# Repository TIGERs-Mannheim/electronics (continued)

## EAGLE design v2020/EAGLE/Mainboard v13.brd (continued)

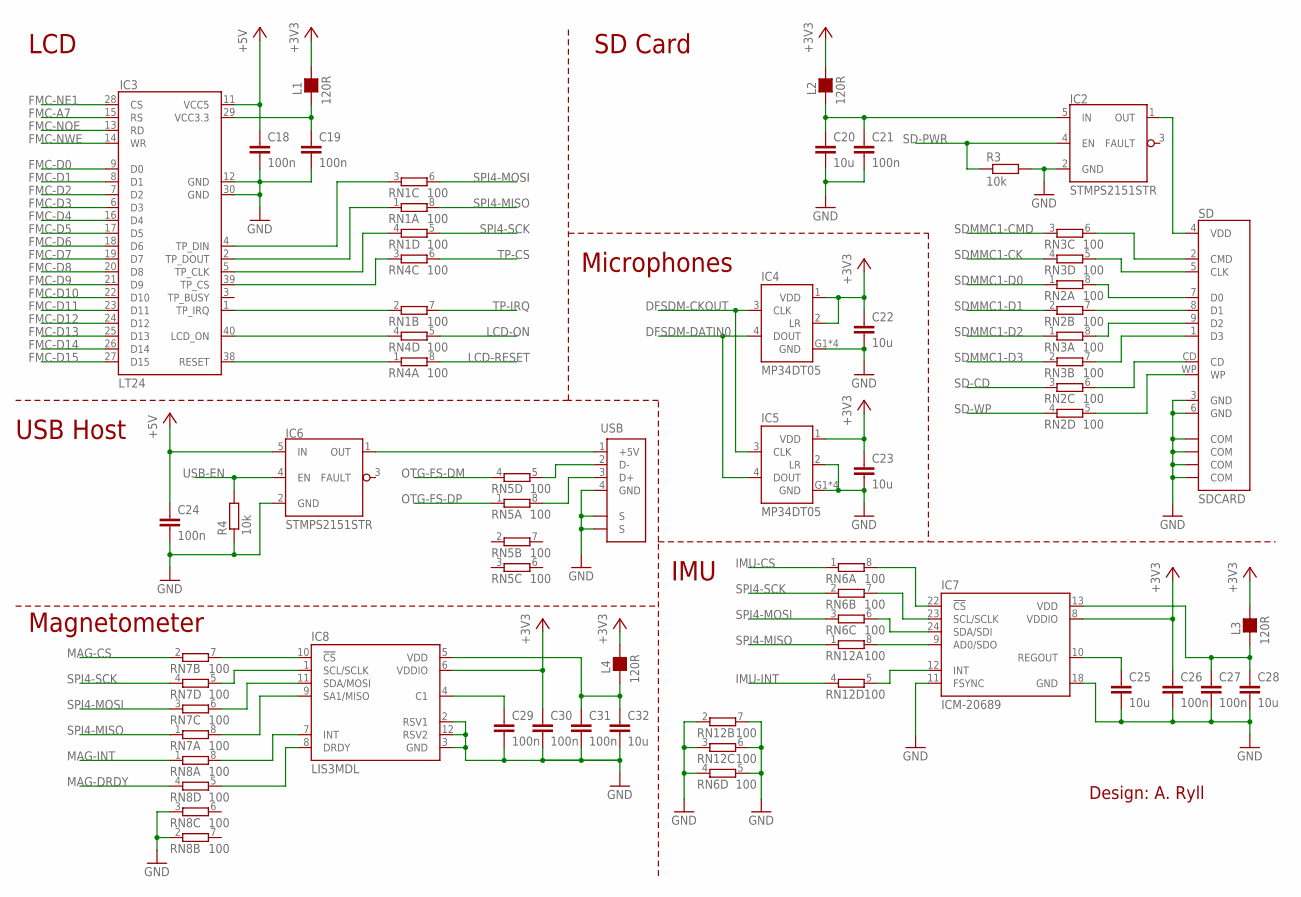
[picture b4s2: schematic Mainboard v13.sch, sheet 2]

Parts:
C18, C19, C21, C24, C26, C27, C29, C30, C31: 100n; C0603
C20, C22, C23, C25, C28, C32: 10u; C0603
IC2, IC6: STMPS2151STR; SOT23-5
IC3: LT24
IC4, IC5: MP34DT05; HCLGA4
IC7: ICM-20689; QFN24-4X4-P
IC8: LIS3MDL; VFLGA-12
L1, L2, L3, L4: 120R; L0603
R3, R4: 10k; R0603
RN1, RN2, RN3, RN4, RN5, RN6, RN7, RN8, RN12: 100; EXB28V
SD: SDCARD
USB: USBATE; USBA-TE

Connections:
+3V3: C22.1, C23.1, C26.1, C30.1, IC4.1 (VDD), IC4.2 (LR), IC5.1 (VDD), IC7.8 (VDDIO), IC8.6 (VDDIO), L1.2, L2.2, L3.2, L4.2; also elsewhere on the board
+5V: C18.1, C24.1, IC3.11 (VCC5), IC6.5 (IN); also elsewhere on the board
DFSDM-CKOUT: IC4.3 (CLK), IC5.3 (CLK); also elsewhere on the board
DFSDM-DATIN0: IC4.4 (DOUT), IC5.4 (DOUT); also elsewhere on the board
FMC-A7: IC3.15 (RS); also elsewhere on the board
FMC-D0: IC3.9 (D0); also elsewhere on the board
FMC-D1: IC3.8 (D1); also elsewhere on the board
FMC-D2: IC3.7 (D2); also elsewhere on the board
FMC-D3: IC3.6 (D3); also elsewhere on the board
FMC-D4: IC3.16 (D4); also elsewhere on the board
FMC-D5: IC3.17 (D5); also elsewhere on the board
FMC-D6: IC3.18 (D6); also elsewhere on the board
FMC-D7: IC3.19 (D7); also elsewhere on the board
FMC-D8: IC3.20 (D8); also elsewhere on the board
FMC-D9: IC3.21 (D9); also elsewhere on the board
FMC-D10: IC3.22 (D10); also elsewhere on the board
FMC-D11: IC3.23 (D11); also elsewhere on the board
FMC-D12: IC3.24 (D12); also elsewhere on the board
FMC-D13: IC3.25 (D13); also elsewhere on the board
FMC-D14: IC3.26 (D14); also elsewhere on the board
FMC-D15: IC3.27 (D15); also elsewhere on the board
FMC-NE1: IC3.28 (CS); also elsewhere on the board
FMC-NOE: IC3.13 (RD); also elsewhere on the board
FMC-NWE: IC3.14 (WR); also elsewhere on the board
GND: C18.2, C19.2, C20.2, C21.2, C22.2, C23.2, C24.2, C25.2, C26.2, C27.2, C28.2, C29.2, C30.2, C31.2, C32.2, IC2.2 (GND), IC3.12 (GND), IC3.30 (GND), IC4.G1 (GND), IC4.G2 (GND), IC4.G3 (GND), IC4.G4 (GND), IC5.2 (LR), IC5.G1 (GND), IC5.G2 (GND), IC5.G3 (GND), IC5.G4 (GND), IC6.2 (GND), IC7.11 (FSYNC), IC7.18 (GND), IC8.2 (RSV1), IC8.3 (GND), IC8.12 (RSV2), R3.2, R4.1, RN6.4 (1), RN6.5 (2), RN8.2 (1), RN8.3 (1), RN12.2 (1), RN12.3 (1), RN12.6 (2), RN12.7 (2), SD.3 (GND), SD.6 (GND), SD.COM1 (COM), SD.COM2 (COM), SD.COM3 (COM), SD.COM4 (COM), USB.4 (GND), USB.MNT1 (S), USB.MNT2 (S); also elsewhere on the board
IMU-CS: RN6.1; also elsewhere on the board
IMU-INT: RN12.4 (1); also elsewhere on the board
LCD-ON: RN4.5 (2); also elsewhere on the board
LCD-RESET: RN4.8 (2); also elsewhere on the board
MAG-CS: RN7.2 (1); also elsewhere on the board
MAG-DRDY: RN8.4 (1); also elsewhere on the board
MAG-INT: RN8.1; also elsewhere on the board
unnamed: IC8.10 (!CS), RN7.7 (2)
unnamed: IC8.1 (SCL/SCLK), RN7.5 (2)
unnamed: IC8.11 (SDA/MOSI), RN7.6 (2)
unnamed: IC8.9 (SA1/MISO), RN7.8 (2)
unnamed: IC8.7 (INT), RN8.8 (2)
unnamed: IC8.8 (DRDY), RN8.5 (2)
unnamed: C29.1, IC8.4 (C1)
unnamed: C31.1, C32.1, IC8.5 (VDD), L4.1
unnamed: IC7.12 (INT), RN12.5 (2)
unnamed: C19.1, IC3.29 (VCC3.3), L1.1
unnamed: IC3.38 (RESET), RN4.1
unnamed: IC3.40 (LCD_ON), RN4.4 (1)
unnamed: IC3.1 (TP_IRQ), RN1.2 (1)
unnamed: IC3.39 (TP_CS), RN4.3 (1)
unnamed: IC3.5 (TP_CLK), RN1.4 (1)
unnamed: IC3.2 (TP_DOUT), RN1.1
unnamed: IC3.4 (TP_DIN), RN1.3 (1)
unnamed: RN2.7 (2), SD.8 (D1)
unnamed: RN2.8 (2), SD.7 (D0)
unnamed: RN3.5 (2), SD.5 (CLK)
unnamed: RN3.6 (2), SD.2 (CMD)
unnamed: RN3.8 (2), SD.9 (D2)
unnamed: RN3.7 (2), SD.1 (D3)
unnamed: RN2.6 (2), SD.CD
unnamed: RN2.5 (2), SD.WP
unnamed: C20.1, C21.1, IC2.5 (IN), L2.1
unnamed: IC6.1 (OUT), USB.1 (+5V)
unnamed: RN5.5 (2), USB.2 (D-)
unnamed: RN5.8 (2), USB.3 (D+)
unnamed: IC7.9 (AD0/SDO), RN12.8 (2)
unnamed: C25.1, IC7.10 (REGOUT)
unnamed: C27.1, C28.1, IC7.13 (VDD), L3.1
unnamed: IC7.24 (SDA/SDI), RN6.6 (2)
unnamed: IC7.23 (SCL/SCLK), RN6.7 (2)
unnamed: IC7.22 (!CS), RN6.8 (2)
OTG-FS-DM: RN5.4 (1); also elsewhere on the board
OTG-FS-DP: RN5.1; also elsewhere on the board
SD-CD: RN2.3 (1); also elsewhere on the board
SD-PWR: IC2.4 (EN), R3.1; also elsewhere on the board
SD-WP: RN2.4 (1); also elsewhere on the board
SDMMC1-CK: RN3.4 (1); also elsewhere on the board
SDMMC1-CMD: RN3.3 (1); also elsewhere on the board
SDMMC1-D0: RN2.1; also elsewhere on the board
SDMMC1-D1: RN2.2 (1); also elsewhere on the board
SDMMC1-D2: RN3.1; also elsewhere on the board
SDMMC1-D3: RN3.2 (1); also elsewhere on the board
SD_PWR: IC2.1 (OUT), SD.4 (VDD)
SPI4-MISO: RN1.8 (2), RN7.1, RN12.1; also elsewhere on the board
SPI4-MOSI: RN1.6 (2), RN6.3 (1), RN7.3 (1); also elsewhere on the board
SPI4-SCK: RN1.5 (2), RN6.2 (1), RN7.4 (1); also elsewhere on the board
TP-CS: RN4.6 (2); also elsewhere on the board
TP-IRQ: RN1.7 (2); also elsewhere on the board
USB-EN: IC6.4 (EN), R4.2; also elsewhere on the board

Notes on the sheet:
Design: A. Ryll
LCD
Microphones
SD Card
USB Host
Magnetometer
IMU

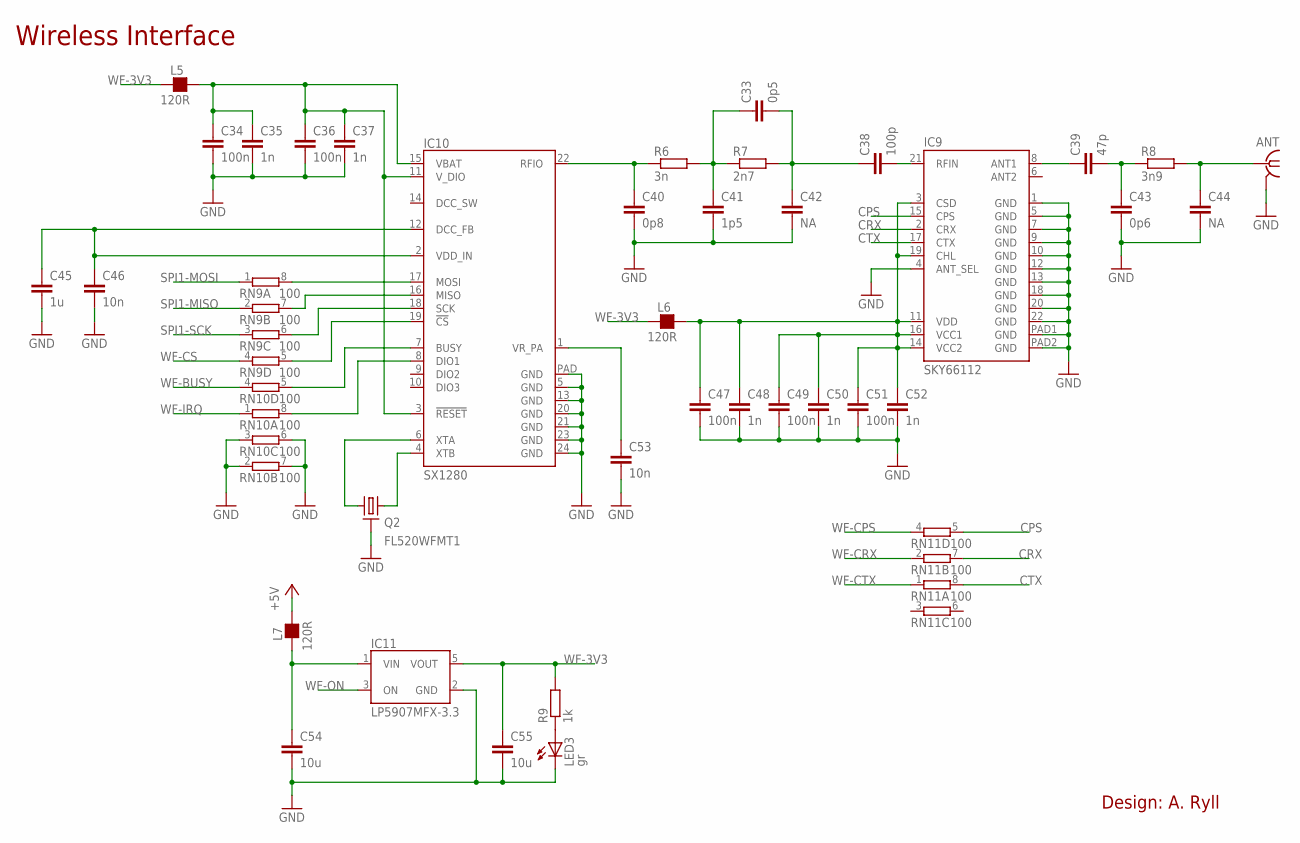
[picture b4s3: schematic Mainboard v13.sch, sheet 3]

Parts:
ANT: ANT-SMARA; ANT-SMA-RA
C33: 0p5; C0402
C34, C36, C47, C49, C51: 100n; C0603
C35, C37, C48, C50, C52: 1n; C0603
C38: 100p; C0402
C39: 47p; C0402
C40: 0p8; C0402
C41: 1p5; C0402
C42, C44: NA; C0402
C43: 0p6; C0402
C45: 1u; C0603
C46, C53: 10n; C0603
C54, C55: 10u; C0603
IC9: SKY66112; SMCM-22
IC10: SX1280; QFN24L
IC11: LP5907MFX-3.3; SOT23-5L
L5, L6, L7: 120R; L0603
LED3: gr; CHIP-LED0603
Q2: FL520WFMT1; CRYSTAL-7M
R6: 3n; R0402
R7: 2n7; R0402
R8: 3n9; R0402
R9: 1k; R0603
RN9, RN10, RN11: 100; EXB28V

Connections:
+5V: L7.2; also elsewhere on the board
CPS: IC9.15 (CPS), RN11.5 (2)
CRX: IC9.2 (CRX), RN11.7 (2)
CTX: IC9.17 (CTX), RN11.8 (2)
GND: ANT.GND1 (GND), ANT.GND2 (GND), ANT.GND3 (GND), ANT.GND4 (GND), C34.2, C35.2, C36.2, C37.2, C40.2, C41.2, C42.2, C43.2, C44.2, C45.2, C46.2, C47.2, C48.2, C49.2, C50.2, C51.2, C52.2, C53.2, C54.2, C55.2, IC9.1 (GND), IC9.4 (ANT_SEL), IC9.5 (GND), IC9.7 (GND), IC9.9 (GND), IC9.10 (GND), IC9.12 (GND), IC9.13 (GND), IC9.18 (GND), IC9.20 (GND), IC9.22 (GND), IC9.PAD1 (GND), IC9.PAD2 (GND), IC10.5 (GND), IC10.13 (GND), IC10.20 (GND), IC10.21 (GND), IC10.23 (GND), IC10.24 (GND), IC10.PAD (GND), IC11.2 (GND), LED3.C, Q2.2 (GND1), Q2.4 (GND1), RN10.2 (1), RN10.3 (1), RN10.6 (2), RN10.7 (2); also elsewhere on the board
unnamed: LED3.A, R9.1
unnamed: C54.1, IC11.1 (VIN), L7.1
unnamed: IC10.17 (MOSI), RN9.8 (2)
unnamed: IC10.16 (MISO), RN9.7 (2)
unnamed: IC10.18 (SCK), RN9.6 (2)
unnamed: IC10.19 (!CS), RN9.5 (2)
unnamed: IC10.7 (BUSY), RN10.5 (2)
unnamed: IC10.8 (DIO1), RN10.8 (2)
unnamed: IC10.4 (XTB), Q2.3 (2)
unnamed: IC10.6 (XTA), Q2.1
unnamed: C45.1, C46.1, IC10.2 (VDD_IN), IC10.12 (DCC_FB)
unnamed: C53.1, IC10.1 (VR_PA)
unnamed: C38.2, IC9.21 (RFIN)
unnamed: C33.1, C41.1, R6.2, R7.1
unnamed: C33.2, C38.1, C42.1, R7.2
unnamed: C40.1, IC10.22 (RFIO), R6.1
unnamed: C39.1, IC9.8 (ANT1)
unnamed: C39.2, C43.1, R8.1
unnamed: ANT.C (1), C44.1, R8.2
SPI1-MISO: RN9.2 (1); also elsewhere on the board
SPI1-MOSI: RN9.1; also elsewhere on the board
SPI1-SCK: RN9.3 (1); also elsewhere on the board
WF-3V3: C55.1, IC11.5 (VOUT), L5.1, L6.1, R9.2
WF-BUSY: RN10.4 (1); also elsewhere on the board
WF-CPS: RN11.4 (1); also elsewhere on the board
WF-CRX: RN11.2 (1); also elsewhere on the board
WF-CS: RN9.4 (1); also elsewhere on the board
WF-CTX: RN11.1; also elsewhere on the board
WF-IRQ: RN10.1; also elsewhere on the board
WF-ON: IC11.3 (ON); also elsewhere on the board
WF_3V3FEM: C47.1, C48.1, C49.1, C50.1, C51.1, C52.1, IC9.3 (CSD), IC9.11 (VDD), IC9.14 (VCC2), IC9.16 (VCC1), IC9.19 (CHL), L6.2
WF_3V3SX: C34.1, C35.1, C36.1, C37.1, IC10.3 (!RESET), IC10.11 (V_DIO), IC10.15 (VBAT), L5.2

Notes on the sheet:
Design: A. Ryll
Wireless Interface

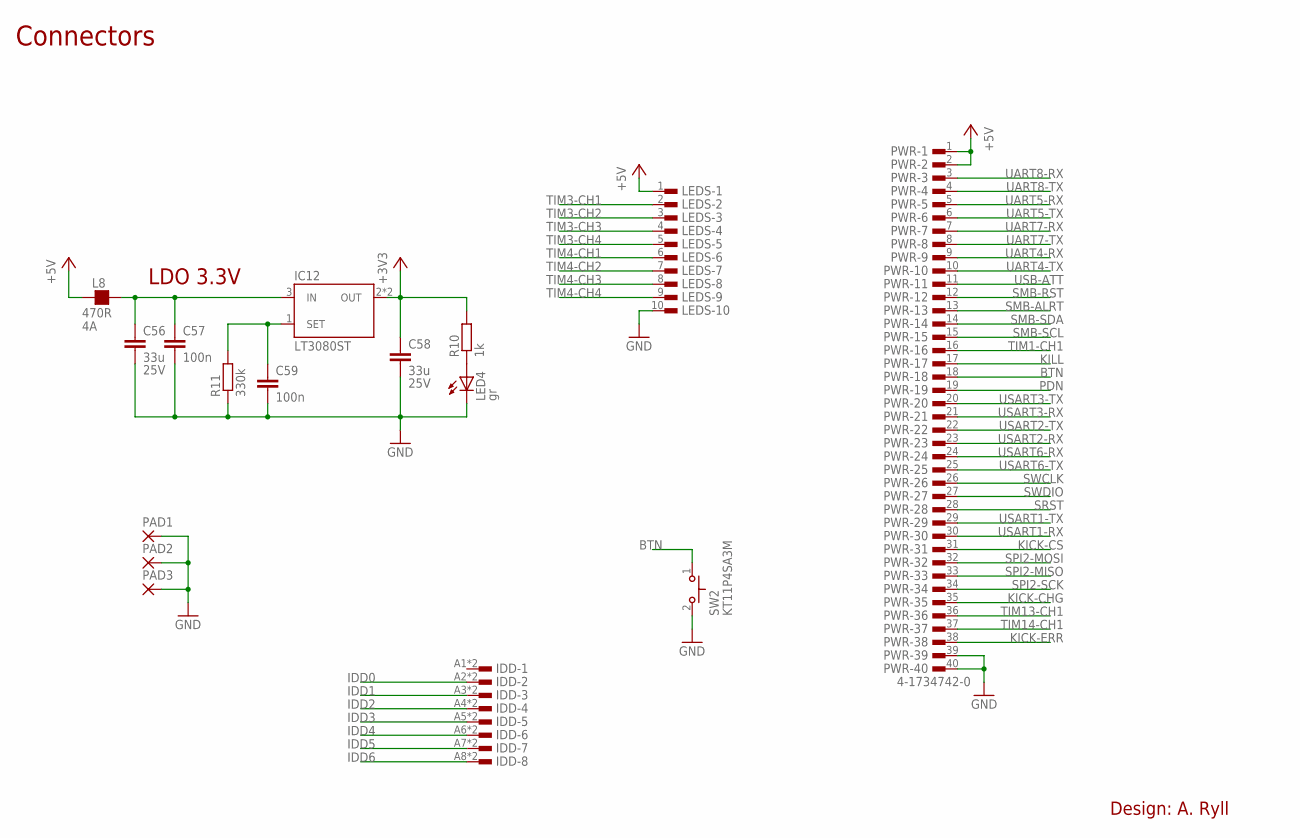
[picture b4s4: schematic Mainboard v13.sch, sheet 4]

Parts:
C56, C58: 33u; C1206; VOLTAGE 25V
C57, C59: 100n; C0603
IC12: LT3080ST; SOT223
IDD: TE-FPC-1MM-8V; TE-1734248-8
L8: 470R; L1206
LED4: gr; CHIP-LED0603
LEDS: TE-FPC-1MM-10H; TE-1-84952-0
PAD1, PAD2, PAD3: WIREPAD5,4/3,0; 5,4/3,0
PWR: 4-1734742-0; TE-4-1734592-0
R10: 1k; R0603
R11: 330k; R0603
SW2: KT11P4SA3M; KT11

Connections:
+3V3: C58.1, IC12.2 (OUT), IC12.4 (OUT), R10.2; also elsewhere on the board
+5V: L8.1, LEDS.1, PWR.1, PWR.2; also elsewhere on the board
BTN: PWR.18, SW2.1
GND: C56.2, C57.2, C58.2, C59.2, LED4.C, LEDS.10, PAD1.1, PAD1.2, PAD2.1, PAD2.2, PAD3.1, PAD3.2, PWR.39, PWR.40, R11.1, SW2.2; also elsewhere on the board
IDD0: IDD.A2, IDD.B2; also elsewhere on the board
IDD1: IDD.A3, IDD.B3; also elsewhere on the board
IDD2: IDD.A4, IDD.B4; also elsewhere on the board
IDD3: IDD.A5, IDD.B5; also elsewhere on the board
IDD4: IDD.A6, IDD.B6; also elsewhere on the board
IDD5: IDD.A7, IDD.B7; also elsewhere on the board
IDD6: IDD.A8, IDD.B8; also elsewhere on the board
KICK-CHG: PWR.35; also elsewhere on the board
KICK-CS: PWR.31; also elsewhere on the board
KICK-ERR: PWR.38; also elsewhere on the board
KILL: PWR.17; also elsewhere on the board
unnamed: C59.1, IC12.1 (SET), R11.2
unnamed: LED4.A, R10.1
unnamed: C56.1, C57.1, IC12.3 (IN), L8.2
PDN: PWR.19; also elsewhere on the board
SMB-ALRT: PWR.13; also elsewhere on the board
SMB-RST: PWR.12; also elsewhere on the board
SMB-SCL: PWR.15; also elsewhere on the board
SMB-SDA: PWR.14; also elsewhere on the board
SPI2-MISO: PWR.33; also elsewhere on the board
SPI2-MOSI: PWR.32; also elsewhere on the board
SPI2-SCK: PWR.34; also elsewhere on the board
SRST: PWR.28; also elsewhere on the board
SWCLK: PWR.26; also elsewhere on the board
SWDIO: PWR.27; also elsewhere on the board
TIM1-CH1: PWR.16; also elsewhere on the board
TIM3-CH1: LEDS.2; also elsewhere on the board
TIM3-CH2: LEDS.3; also elsewhere on the board
TIM3-CH3: LEDS.4; also elsewhere on the board
TIM3-CH4: LEDS.5; also elsewhere on the board
TIM4-CH1: LEDS.6; also elsewhere on the board
TIM4-CH2: LEDS.7; also elsewhere on the board
TIM4-CH3: LEDS.8; also elsewhere on the board
TIM4-CH4: LEDS.9; also elsewhere on the board
TIM13-CH1: PWR.36; also elsewhere on the board
TIM14-CH1: PWR.37; also elsewhere on the board
UART4-RX: PWR.9; also elsewhere on the board
UART4-TX: PWR.10; also elsewhere on the board
UART5-RX: PWR.5; also elsewhere on the board
UART5-TX: PWR.6; also elsewhere on the board
UART7-RX: PWR.7; also elsewhere on the board
UART7-TX: PWR.8; also elsewhere on the board
UART8-RX: PWR.3; also elsewhere on the board
UART8-TX: PWR.4; also elsewhere on the board
USART1-RX: PWR.30; also elsewhere on the board
USART1-TX: PWR.29; also elsewhere on the board
USART2-RX: PWR.23; also elsewhere on the board
USART2-TX: PWR.22; also elsewhere on the board
USART3-RX: PWR.21; also elsewhere on the board
USART3-TX: PWR.20; also elsewhere on the board
USART6-RX: PWR.24; also elsewhere on the board
USART6-TX: PWR.25; also elsewhere on the board
USB-ATT: PWR.11; also elsewhere on the board

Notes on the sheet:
LDO 3.3V
Design: A. Ryll
Connectors

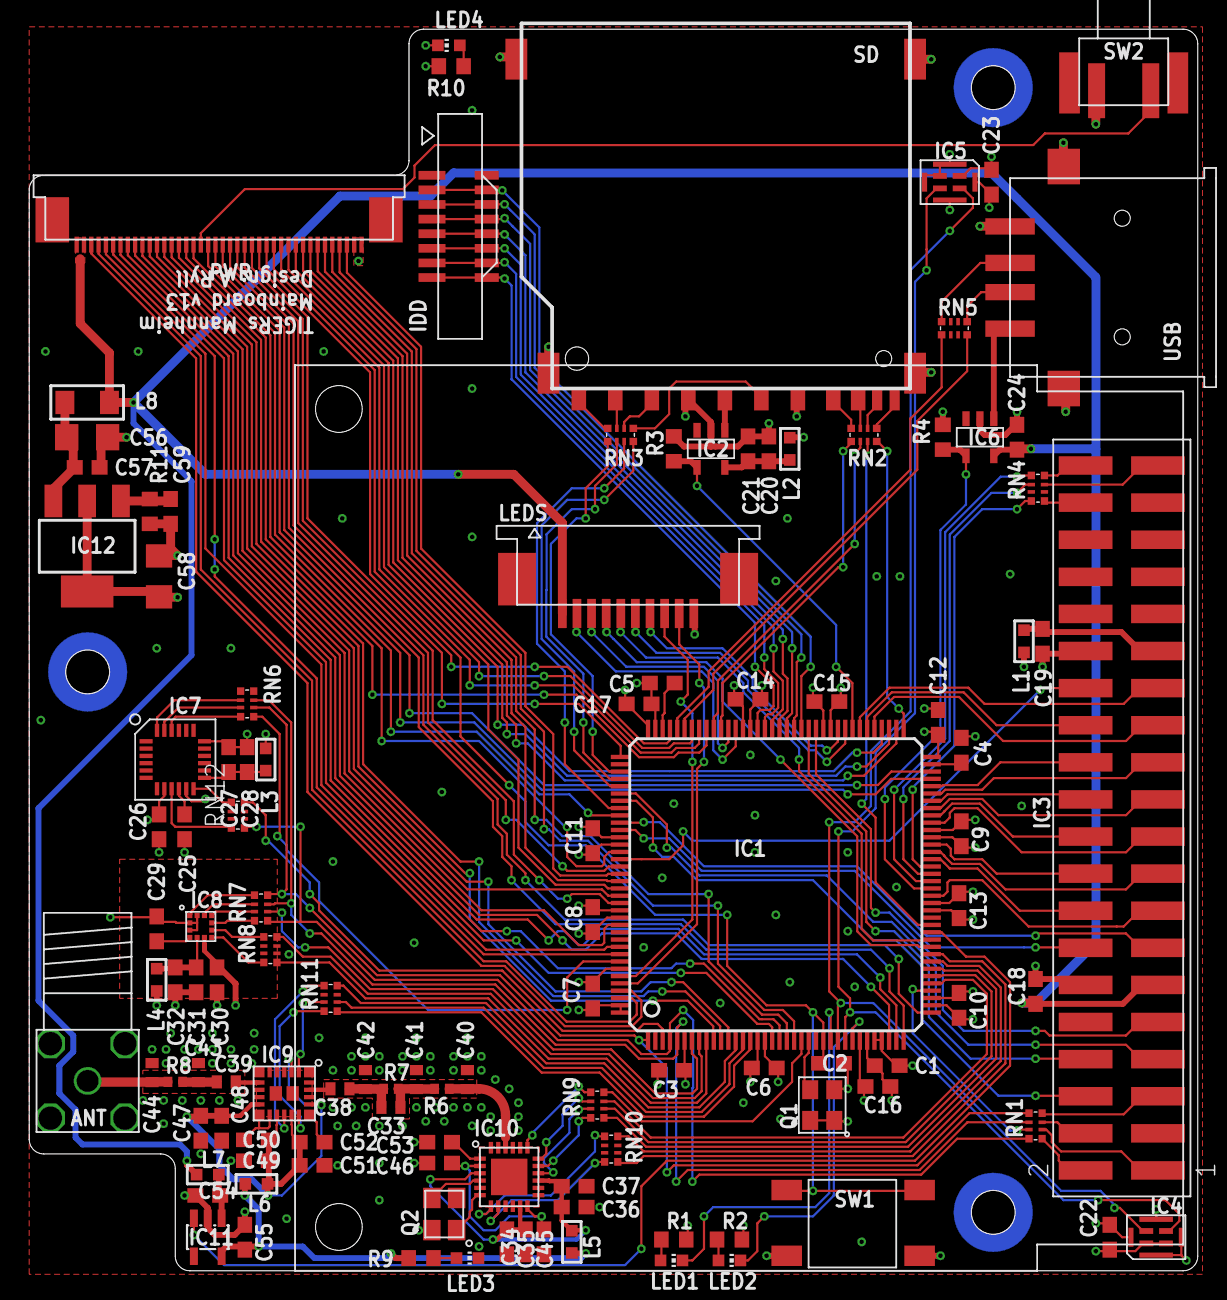
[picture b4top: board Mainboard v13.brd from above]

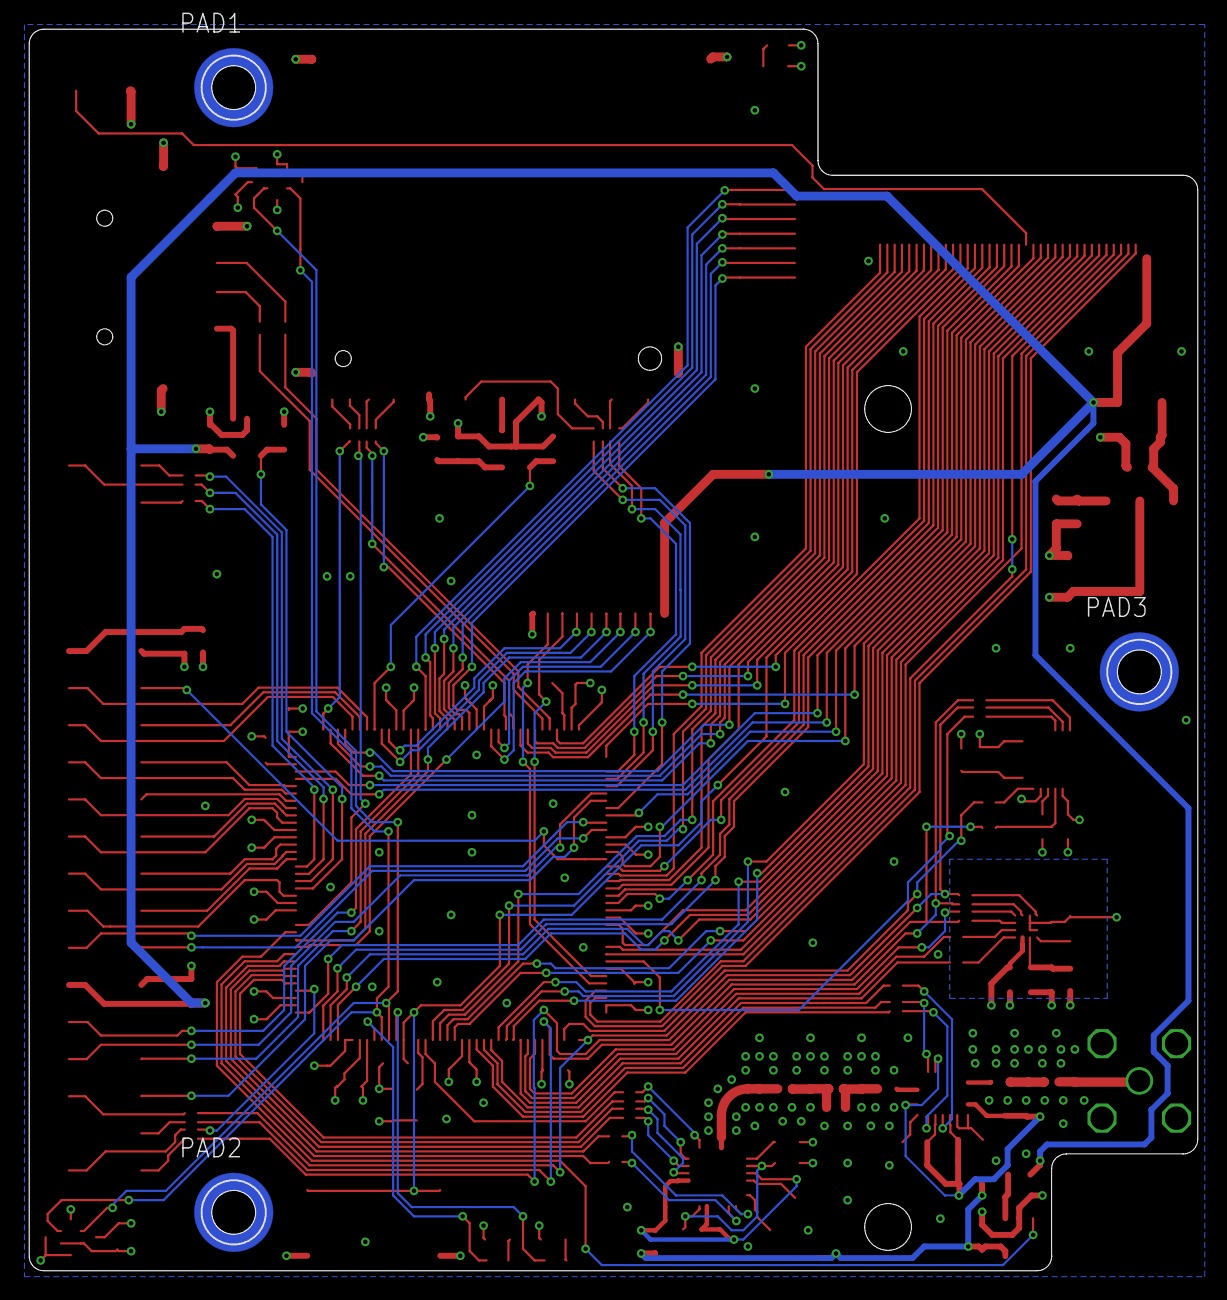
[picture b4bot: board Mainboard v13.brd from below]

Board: 4 copper layers, 80.0 x 85.0 mm, 118 parts (3 on the bottom side), 181 nets.
